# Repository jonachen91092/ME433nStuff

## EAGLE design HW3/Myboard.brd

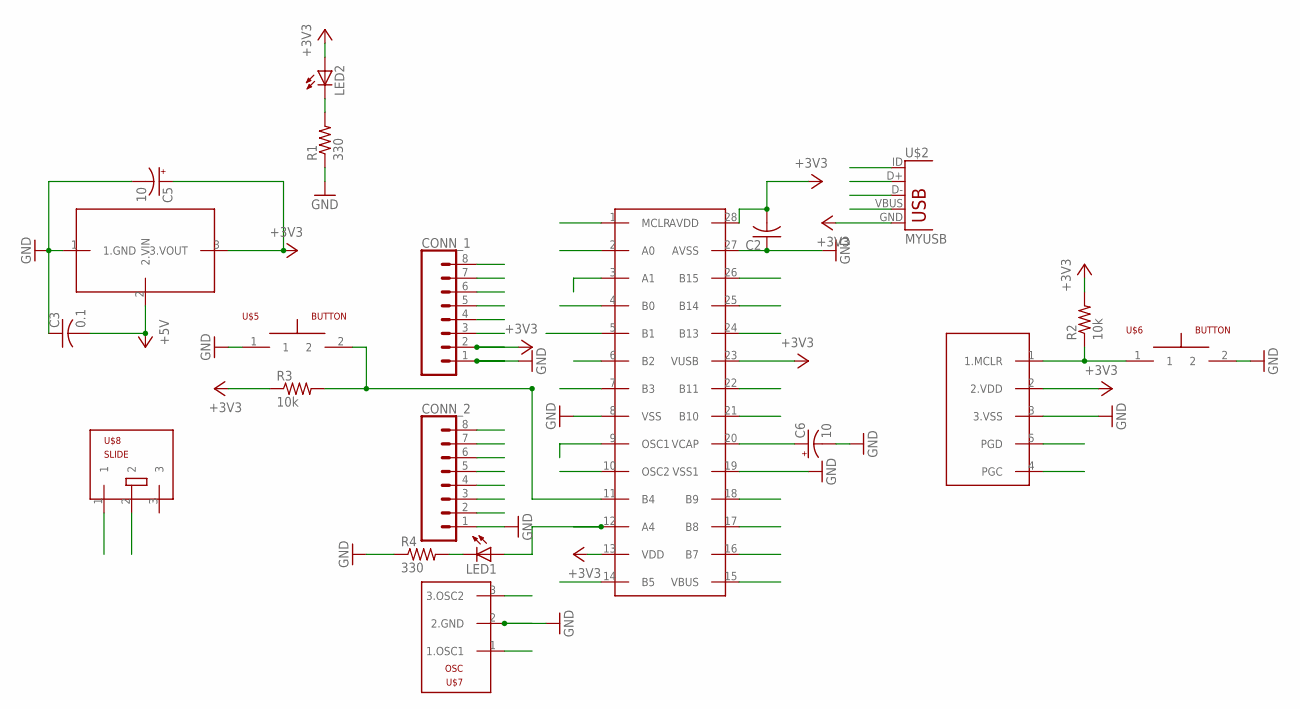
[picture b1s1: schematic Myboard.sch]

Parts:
C2: C-US025-025X050; C025-025X050
C3: 0.1; C025-025X050
C5, C6: 10; B45181B
CONN_1, CONN_2: CONN_08"; 1X08
LED1, LED2: LED3MM
R1, R4: 330; 0207/10
R2, R3: 10k; 0207/10
U$1: PIC; DIL28-3
U$2: MYUSB; USB-MB-H
U$3: MCP1702; TO92
U$4: SWITCH_M05; 1X05
U$5, U$6: BUTTON
U$7: OSC
U$8: SLIDE

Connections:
+3V3: C2.2, C5.+, CONN_1.2, LED2.A, R2.2, R3.1, U$1.13 (VDD), U$1.23 (VUSB), U$1.28 (AVDD), U$2.GND, U$3.3 (3.VOUT), U$4.2 (2.VDD)
A0: CONN_1.8, U$1.2 (A0)
A1: CONN_1.7, U$1.3 (A1)
A4: CONN_1.3, LED1.A, U$1.12 (A4)
B0: U$1.4 (B0), U$4.5 (PGD)
B1: U$1.5 (B1), U$4.4 (PGC)
B2: CONN_1.6, U$1.6 (B2)
B3: CONN_1.5, U$1.7 (B3)
B4: CONN_1.4, R3.2, U$1.11 (B4), U$5.2
B5: U$1.14 (B5), U$2.ID
B7: CONN_2.3, U$1.16 (B7)
B8: CONN_2.4, U$1.17 (B8)
B9: CONN_2.5, U$1.18 (B9)
B10: U$1.21 (B10), U$2.D+
B11: U$1.22 (B11), U$2.D-
B13: CONN_2.6, U$1.24 (B13)
B14: CONN_2.7, U$1.25 (B14)
B15: CONN_2.8, U$1.26 (B15)
GND: C2.1, C3.1, C5.-, C6.-, CONN_1.1, CONN_2.1, R1.1, R4.1, U$1.8 (VSS), U$1.19 (VSS1), U$1.27 (AVSS), U$3.1 (1.GND), U$4.3 (3.VSS), U$5.1, U$6.2, U$7.2 (2.GND)
MCLR: R2.1, U$1.1 (MCLR), U$4.1 (1.MCLR), U$6.1
unnamed: C6.+, U$1.20 (VCAP)
unnamed: LED2.K (C), R1.2
unnamed: LED1.K (C), R4.2
OSC1: U$1.9 (OSC1), U$7.1 (1.OSC1)
OSC2: U$1.10 (OSC2), U$7.3 (3.OSC2)
SW: U$2.VBUS, U$8.1
VBUS: C3.2, CONN_2.2, U$1.15 (VBUS), U$3.2 (2.VIN), U$8.2

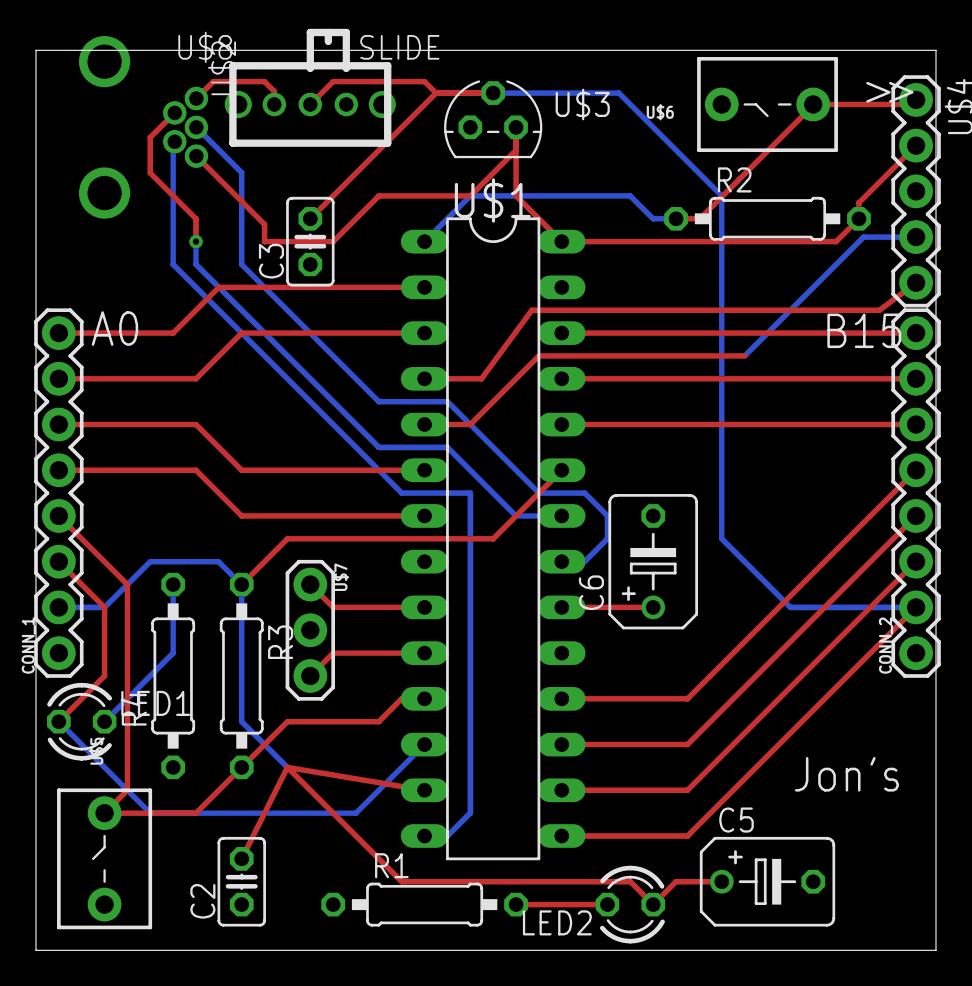
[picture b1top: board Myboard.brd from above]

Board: 2 copper layers, 50.0 x 50.0 mm, 20 parts (0 on the bottom side), 27 nets.

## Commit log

2018-04-10 HW 1
2018-04-10 add pics
2018-04-17 HW2 and 3

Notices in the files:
parts and their libraries:
SparkFun-Connectors: Licensing: Creative Commons ShareAlike 4.0 International - https://creativecommons.org/licenses/by-sa/4.0
